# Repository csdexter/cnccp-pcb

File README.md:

#CNC Control Panel: Schematics and Boards#

(C) 2012 Radu - Eosif Mihailescu <radu.mihailescu@linux360.ro>

All files in this repository except `radu-collected.lbr` are licensed under the
**GNU Generic Public License v3**, a copy of whose text can be accessed
 [here](http://www.gnu.org/licenses/gpl.html).

`radu-collected.lbr` alone is hereby licensed under the **Modified BSD (3-clause) License**, a copy of whose text can be found in the `radu-collected.lbr.license` file.

This repository contains [EDA](http://en.wikipedia.org/wiki/Electronic_design_automation) source files for all of the boards in the *CNC Control Panel* project in CadSoft Eagle 6 format. Only the `.SCH` (schematic) and `.BRD` (board) files are provided as all data needed for manufacturing can easily be derived from the former. No guarantee is made as to which minor version of Eagle was used to save the file, but it *may* be the latest at the time of this writing.

The board description files *may* contain routing information or be supplied unrouted. In the former case, the routing artwork *may* have been generated by either Eagle's internal autorouter or [FreeRouting](http://www.freerouting.net/). A 25mil routing grid and 10/10mil trace/space settings will have been used in both cases.

All files included here are compatible with the free version of Eagle (i.e. describe PCBs having no more than 2 layers and measuring no more than 10cm by 8cm each).

Git tags will be used to mark specific revisions that were actually manufactured so that a correspondence between the evolution of the sources and the status of physical by-products can be maintained.

##WARNING##
*Unless and until explictily noted otherwise, the engineering materials here are laboratory quality and neither intended for manufacturing in production quantities nor for distribution (e.g. as kits) to end-users. The design data here does not explicitly follow any widely-accepted safety/security/EMI regulation or standard, therefore any manufacturing and/or usage in connection with live equipment is entirely at your own risk.*

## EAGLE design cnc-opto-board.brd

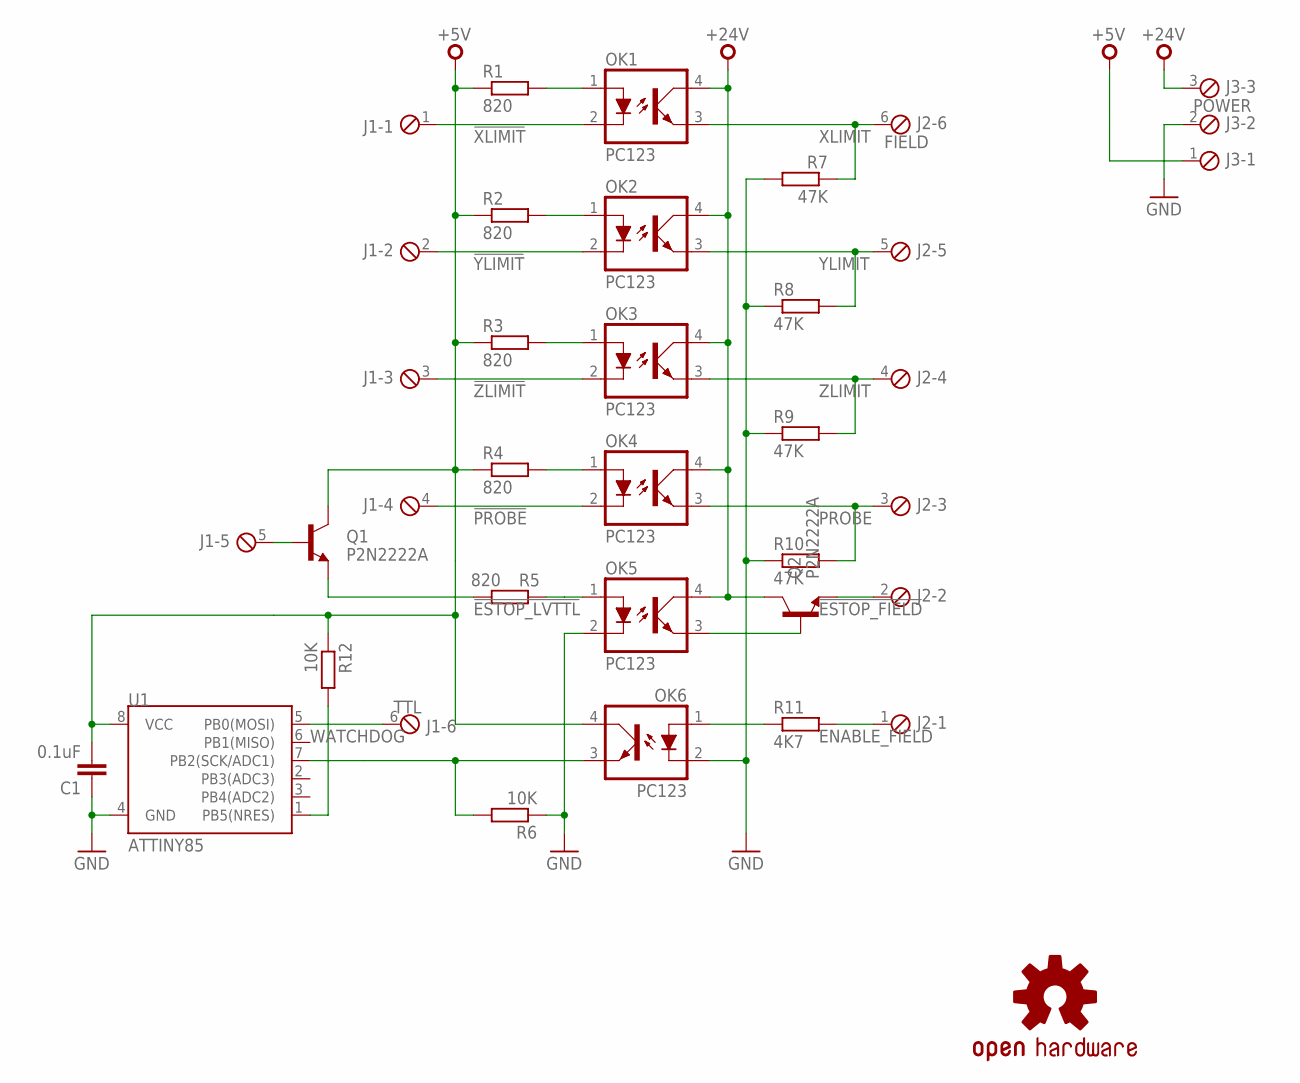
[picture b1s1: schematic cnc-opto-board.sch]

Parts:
C1: 0.1uF; C050-025X075
J1: TTL; MKDS06
J2: FIELD; MKDS06
J3: POWER; MKDS03
LOGO1: OSHW-LOGOL; OSHW-LOGO-L
OK1, OK2, OK3, OK4, OK5, OK6: PC123; DIL04
Q1, Q2: P2N2222A; TO-92
R1, R2, R3, R4, R5: 820; 0207/10
R6, R12: 10K; 0207/10
R7, R8, R9, R10: 47K; 0207/10
R11: 4K7; 0207/10
U1: ATTINY85; DIL08

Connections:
!ESTOP_FIELD: J2.2, Q2.3 (E)
!ESTOP_LVTTL: OK5.1 (A), R5.1
!PROBE: J1.4, OK4.2 (C)
!XLIMIT: J1.1, OK1.2 (C)
!YLIMIT: J1.2, OK2.2 (C)
!ZLIMIT: J1.3, OK3.2 (C)
+5V: C1.2, J3.1, OK6.4 (COL), Q1.1 (C), R1.1, R2.1, R3.1, R4.1, R12.1, U1.8 (VCC)
+24V: J3.3, OK1.4 (COL), OK2.4 (COL), OK3.4 (COL), OK4.4 (COL), OK5.4 (COL), Q2.1 (C)
ENABLE_FIELD: J2.1, R11.2
ENABLE_TTL: OK6.3 (EMIT), R6.2, U1.7 (PB2(SCK/ADC1))
GND: C1.1, J3.2, OK5.2 (C), OK6.2 (C), R6.1, R7.2, R8.1, R9.1, R10.1, U1.4 (GND)
unnamed: OK1.1 (A), R1.2
unnamed: OK2.1 (A), R2.2
unnamed: OK3.1 (A), R3.2
unnamed: OK4.1 (A), R4.2
unnamed: Q1.3 (E), R5.2
unnamed: OK6.1 (A), R11.1
unnamed: J1.5, Q1.2 (B)
unnamed: OK5.3 (EMIT), Q2.2 (B)
unnamed: R12.2, U1.1 (PB5(NRES))
PROBE: J2.3, OK4.3 (EMIT), R10.2
WATCHDOG: J1.6, U1.5 (PB0(MOSI))
XLIMIT: J2.6, OK1.3 (EMIT), R7.1
YLIMIT: J2.5, OK2.3 (EMIT), R8.2
ZLIMIT: J2.4, OK3.3 (EMIT), R9.2

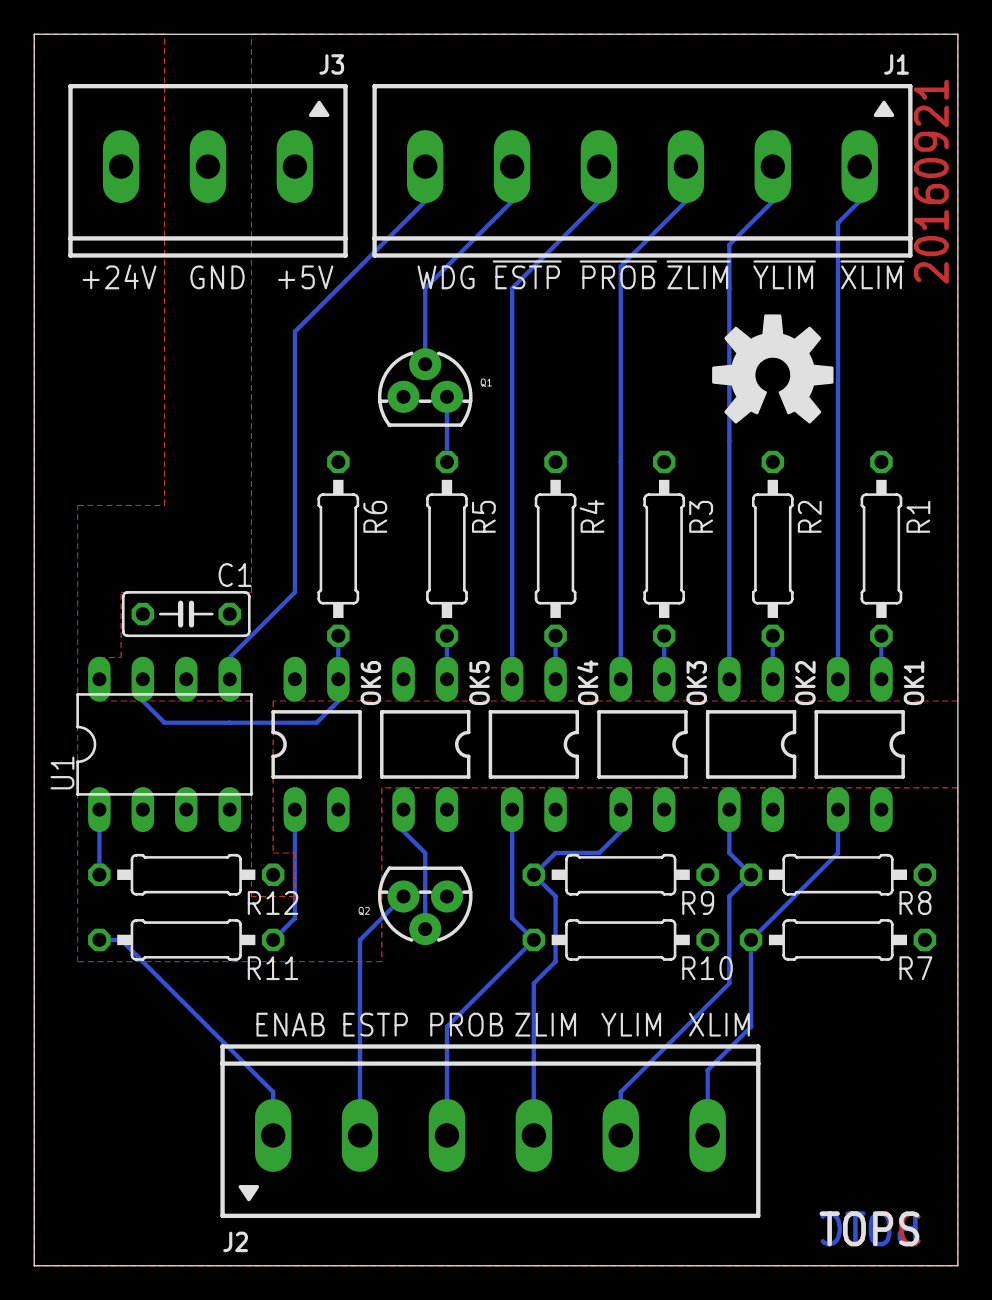
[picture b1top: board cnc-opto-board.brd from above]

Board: 2 copper layers, 54.0 x 72.0 mm, 26 parts (0 on the bottom side), 25 nets.

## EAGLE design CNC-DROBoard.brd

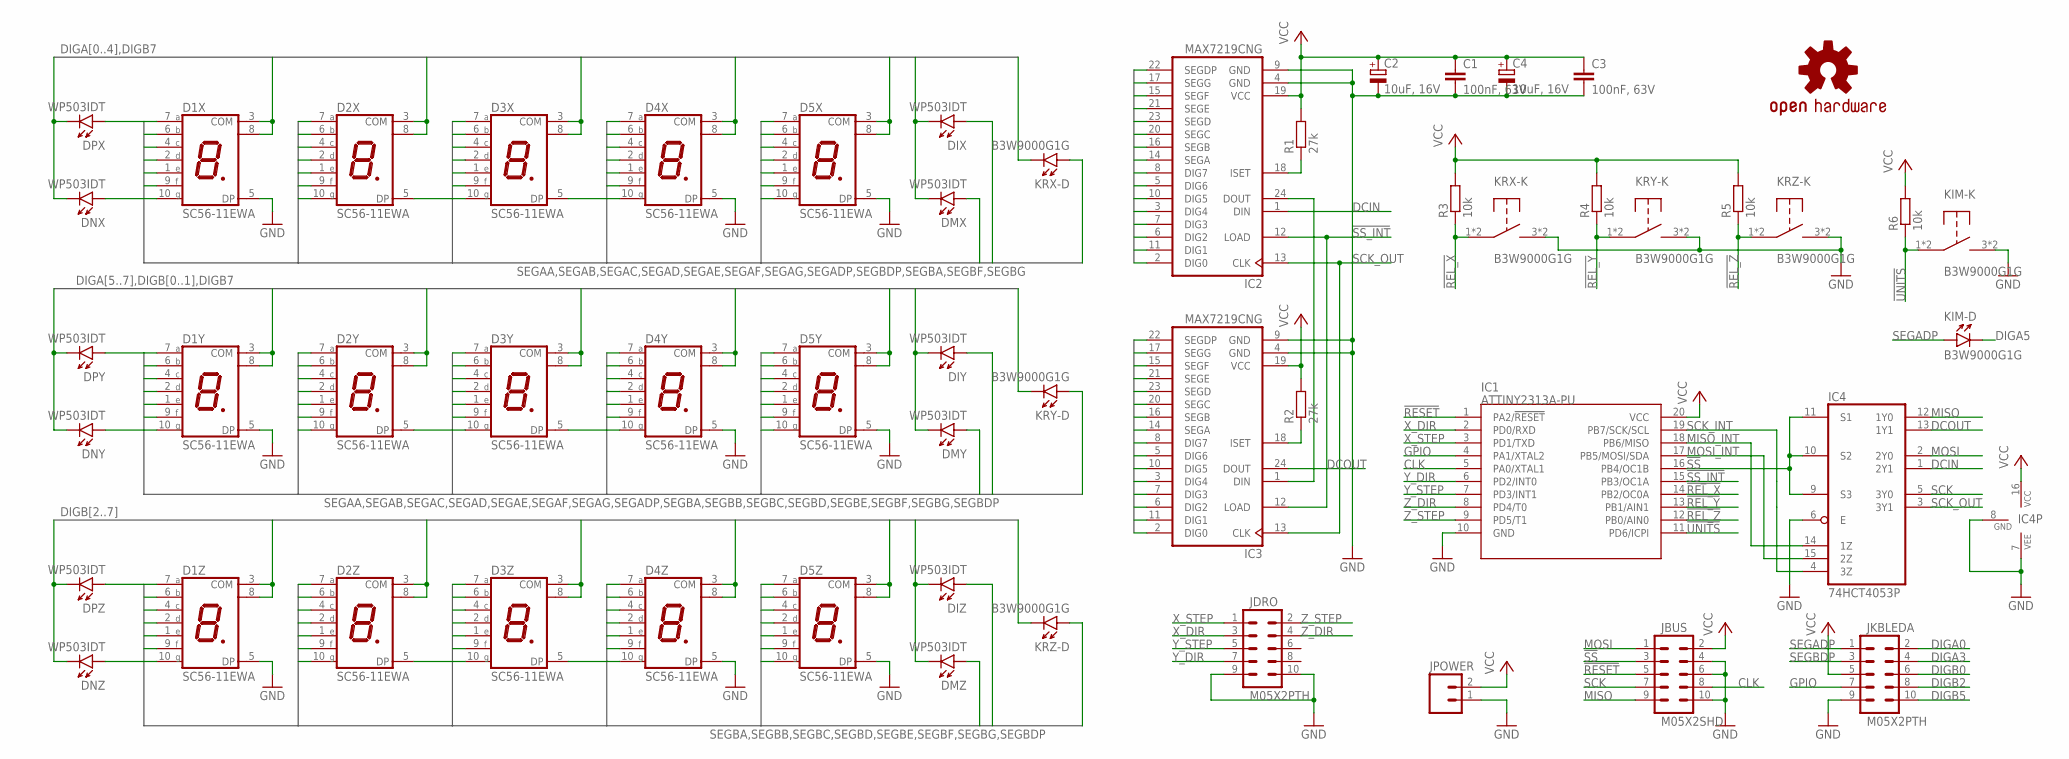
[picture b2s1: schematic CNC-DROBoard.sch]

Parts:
C1, C3: 100nF, 63V; C050-025X075
C2, C4: 10uF, 16V; E2,5-6E
D1X, D1Y, D1Z, D2X, D2Y, D2Z, D3X, D3Y, D3Z, D4X, D4Y, D4Z, D5X, D5Y, D5Z: SC56-11EWA; SA52-11
DIX: WP503IDT; AXIAL__GENERIC_SQ_5X5
DIY: WP503IDT; AXIAL__GENERIC_SQ_5X5
DIZ: WP503IDT; AXIAL__GENERIC_SQ_5X5
DMX: WP503IDT; AXIAL__GENERIC_SQ_5X5
DMY: WP503IDT; AXIAL__GENERIC_SQ_5X5
DMZ: WP503IDT; AXIAL__GENERIC_SQ_5X5
DNX: WP503IDT; AXIAL__GENERIC_SQ_5X5
DNY: WP503IDT; AXIAL__GENERIC_SQ_5X5
DNZ: WP503IDT; AXIAL__GENERIC_SQ_5X5
DPX: WP503IDT; AXIAL__GENERIC_SQ_5X5
DPY: WP503IDT; AXIAL__GENERIC_SQ_5X5
DPZ: WP503IDT; AXIAL__GENERIC_SQ_5X5
IC1: ATTINY2313A-PU; DIL20
IC2, IC3: MAX7219CNG; DIL24-3
IC4: 74HCT4053P; DIL16
JBUS: M05X2SHD; 2X5-SHROUDED
JDRO: M05X2PTH; AVR_ICSP
JKBLEDA: M05X2PTH; AVR_ICSP
JPOWER: M02POLAR; MOLEX-1X2
KIM: B3W9000G1G; OMRON_B3W90
KRX: B3W9000G1G; OMRON_B3W90
KRY: B3W9000G1G; OMRON_B3W90
KRZ: B3W9000G1G; OMRON_B3W90
R1, R2: 27k; 0207/10
R3, R4, R5, R6: 10k; 0207/10
U$1: SPARKFUN_OSHW-LOGOL; SPARKFUN_OSHW-LOGO-L

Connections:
!REL_X: IC1.14 (PB2/OC0A), KRX.1, KRX.2, R3.1
!REL_Y: IC1.13 (PB1/AIN1), KRY.1, KRY.2, R4.1
!REL_Z: IC1.12 (PB0/AIN0), KRZ.1, KRZ.2, R5.1
!RESET: IC1.1 (PA2/!RESET), JBUS.5
!SS: IC1.16 (PB4/OC1B), IC4.9 (S3), IC4.10 (S2), IC4.11 (S1), JBUS.3
!SS_INT: IC1.15 (PB3/OC1A), IC2.12 (LOAD), IC3.12 (LOAD)
!UNITS: IC1.11 (PD6/ICPI), KIM.1, KIM.2, R6.1
CLK: IC1.5 (PA0/XTAL1), JBUS.8
DCIN: IC2.1 (DIN), IC4.1 (2Y1)
DCOUT: IC3.24 (DOUT), IC4.13 (1Y1)
DIGA0: D1X.3 (COM), D1X.8 (COM), IC2.2 (DIG0), JKBLEDA.2
DIGA1: D2X.3 (COM), D2X.8 (COM), IC2.11 (DIG1)
DIGA2: D3X.3 (COM), D3X.8 (COM), IC2.6 (DIG2)
DIGA3: D4X.3 (COM), D4X.8 (COM), IC2.7 (DIG3), JKBLEDA.4
DIGA4: D5X.3 (COM), D5X.8 (COM), IC2.3 (DIG4), KRX.6 (K)
DIGA5: D1Y.3 (COM), D1Y.8 (COM), IC2.10 (DIG5), KIM.6 (K)
DIGA6: D2Y.3 (COM), D2Y.8 (COM), IC2.5 (DIG6)
DIGA7: D3Y.3 (COM), D3Y.8 (COM), IC2.8 (DIG7)
DIGB0: D4Y.3 (COM), D4Y.8 (COM), IC3.2 (DIG0), JKBLEDA.6
DIGB1: D5Y.3 (COM), D5Y.8 (COM), IC3.11 (DIG1), KRY.6 (K)
DIGB2: D1Z.3 (COM), D1Z.8 (COM), IC3.6 (DIG2), JKBLEDA.8
DIGB3: D2Z.3 (COM), D2Z.8 (COM), IC3.7 (DIG3)
DIGB4: D3Z.3 (COM), D3Z.8 (COM), IC3.3 (DIG4)
DIGB5: D4Z.3 (COM), D4Z.8 (COM), IC3.10 (DIG5), JKBLEDA.10
DIGB6: D5Z.3 (COM), D5Z.8 (COM), IC3.5 (DIG6), KRZ.6 (K)
DIGB7: DIX.2 (K), DIY.2 (K), DIZ.2 (K), DMX.2 (K), DMY.2 (K), DMZ.2 (K), DNX.2 (K), DNY.2 (K), DNZ.2 (K), DPX.2 (K), DPY.2 (K), DPZ.2 (K), IC3.8 (DIG7)
GND: C1.2, C2.-, C3.2, C4.-, D1X.5 (DP), D1Y.5 (DP), D1Z.5 (DP), D4X.5 (DP), D4Y.5 (DP), D4Z.5 (DP), D5X.5 (DP), D5Y.5 (DP), D5Z.5 (DP), IC1.10 (GND), IC2.4 (GND), IC2.9 (GND), IC3.4 (GND), IC3.9 (GND), IC4.6 (E), IC4.7 (VEE), IC4.8 (GND), JBUS.4, JBUS.6, JBUS.10, JDRO.9, JDRO.10, JKBLEDA.9, JPOWER.1, KIM.3, KIM.4, KRX.3, KRX.4, KRY.3, KRY.4, KRZ.3, KRZ.4
GPIO: IC1.4 (PA1/XTAL2), JKBLEDA.7
MISO: IC4.12 (1Y0), JBUS.9
MISO_INT: IC1.18 (PB6/MISO), IC4.14 (1Z)
MOSI: IC4.2 (2Y0), JBUS.1
MOSI_INT: IC1.17 (PB5/MOSI/SDA), IC4.15 (2Z)
unnamed: IC2.24 (DOUT), IC3.1 (DIN)
unnamed: IC2.18 (ISET), R1.1
unnamed: IC3.18 (ISET), R2.1
SCK: IC4.5 (3Y0), JBUS.7
SCK_INT: IC1.19 (PB7/SCK/SCL), IC4.4 (3Z)
SCK_OUT: IC2.13 (CLK), IC3.13 (CLK), IC4.3 (3Y1)
SEGAA: D1X.7 (A), D1Y.7 (A), D2X.7 (A), D2Y.7 (A), D3X.7 (A), D3Y.7 (A), D4X.7 (A), D5X.7 (A), IC2.14 (SEGA)
SEGAB: D1X.6 (B), D1Y.6 (B), D2X.6 (B), D2Y.6 (B), D3X.6 (B), D3Y.6 (B), D4X.6 (B), D5X.6 (B), IC2.16 (SEGB)
SEGAC: D1X.4 (C), D1Y.4 (C), D2X.4 (C), D2Y.4 (C), D3X.4 (C), D3Y.4 (C), D4X.4 (C), D5X.4 (C), IC2.20 (SEGC)
SEGAD: D1X.2 (D), D1Y.2 (D), D2X.2 (D), D2Y.2 (D), D3X.2 (D), D3Y.2 (D), D4X.2 (D), D5X.2 (D), IC2.23 (SEGD)
SEGADP: D2X.5 (DP), D2Y.5 (DP), D3X.5 (DP), D3Y.5 (DP), IC2.22 (SEGDP), JKBLEDA.1, KIM.5 (A), KRX.5 (A)
SEGAE: D1X.1 (E), D1Y.1 (E), D2X.1 (E), D2Y.1 (E), D3X.1 (E), D3Y.1 (E), D4X.1 (E), D5X.1 (E), IC2.21 (SEGE)
SEGAF: D1X.9 (F), D1Y.9 (F), D2X.9 (F), D2Y.9 (F), D3X.9 (F), D3Y.9 (F), D4X.9 (F), D5X.9 (F), IC2.15 (SEGF)
SEGAG: D1X.10 (G), D1Y.10 (G), D2X.10 (G), D2Y.10 (G), D3X.10 (G), D3Y.10 (G), D4X.10 (G), D5X.10 (G), IC2.17 (SEGG)
SEGBA: D1Z.7 (A), D2Z.7 (A), D3Z.7 (A), D4Y.7 (A), D4Z.7 (A), D5Y.7 (A), D5Z.7 (A), DNX.1 (A), IC3.14 (SEGA)
SEGBB: D1Z.6 (B), D2Z.6 (B), D3Z.6 (B), D4Y.6 (B), D4Z.6 (B), D5Y.6 (B), D5Z.6 (B), DPY.1 (A), IC3.16 (SEGB)
SEGBC: D1Z.4 (C), D2Z.4 (C), D3Z.4 (C), D4Y.4 (C), D4Z.4 (C), D5Y.4 (C), D5Z.4 (C), DNY.1 (A), IC3.20 (SEGC)
SEGBD: D1Z.2 (D), D2Z.2 (D), D3Z.2 (D), D4Y.2 (D), D4Z.2 (D), D5Y.2 (D), D5Z.2 (D), DPZ.1 (A), IC3.23 (SEGD)
SEGBDP: D2Z.5 (DP), D3Z.5 (DP), DPX.1 (A), IC3.22 (SEGDP), JKBLEDA.3, KRY.5 (A), KRZ.5 (A)
SEGBE: D1Z.1 (E), D2Z.1 (E), D3Z.1 (E), D4Y.1 (E), D4Z.1 (E), D5Y.1 (E), D5Z.1 (E), DNZ.1 (A), IC3.21 (SEGE)
SEGBF: D1Z.9 (F), D2Z.9 (F), D3Z.9 (F), D4Y.9 (F), D4Z.9 (F), D5Y.9 (F), D5Z.9 (F), DIX.1 (A), DIY.1 (A), DIZ.1 (A), IC3.15 (SEGF)
SEGBG: D1Z.10 (G), D2Z.10 (G), D3Z.10 (G), D4Y.10 (G), D4Z.10 (G), D5Y.10 (G), D5Z.10 (G), DMX.1 (A), DMY.1 (A), DMZ.1 (A), IC3.17 (SEGG)
VCC: C1.1, C2.+, C3.1, C4.+, IC1.20 (VCC), IC2.19 (VCC), IC3.19 (VCC), IC4.16 (VCC), JBUS.2, JKBLEDA.5, JPOWER.2, R1.2, R2.2, R3.2, R4.2, R5.2, R6.2
X_DIR: IC1.2 (PD0/RXD), JDRO.3
X_STEP: IC1.3 (PD1/TXD), JDRO.1
Y_DIR: IC1.6 (PD2/INT0), JDRO.7
Y_STEP: IC1.7 (PD3/INT1), JDRO.5
Z_DIR: IC1.8 (PD4/T0), JDRO.4
Z_STEP: IC1.9 (PD5/T1), JDRO.2

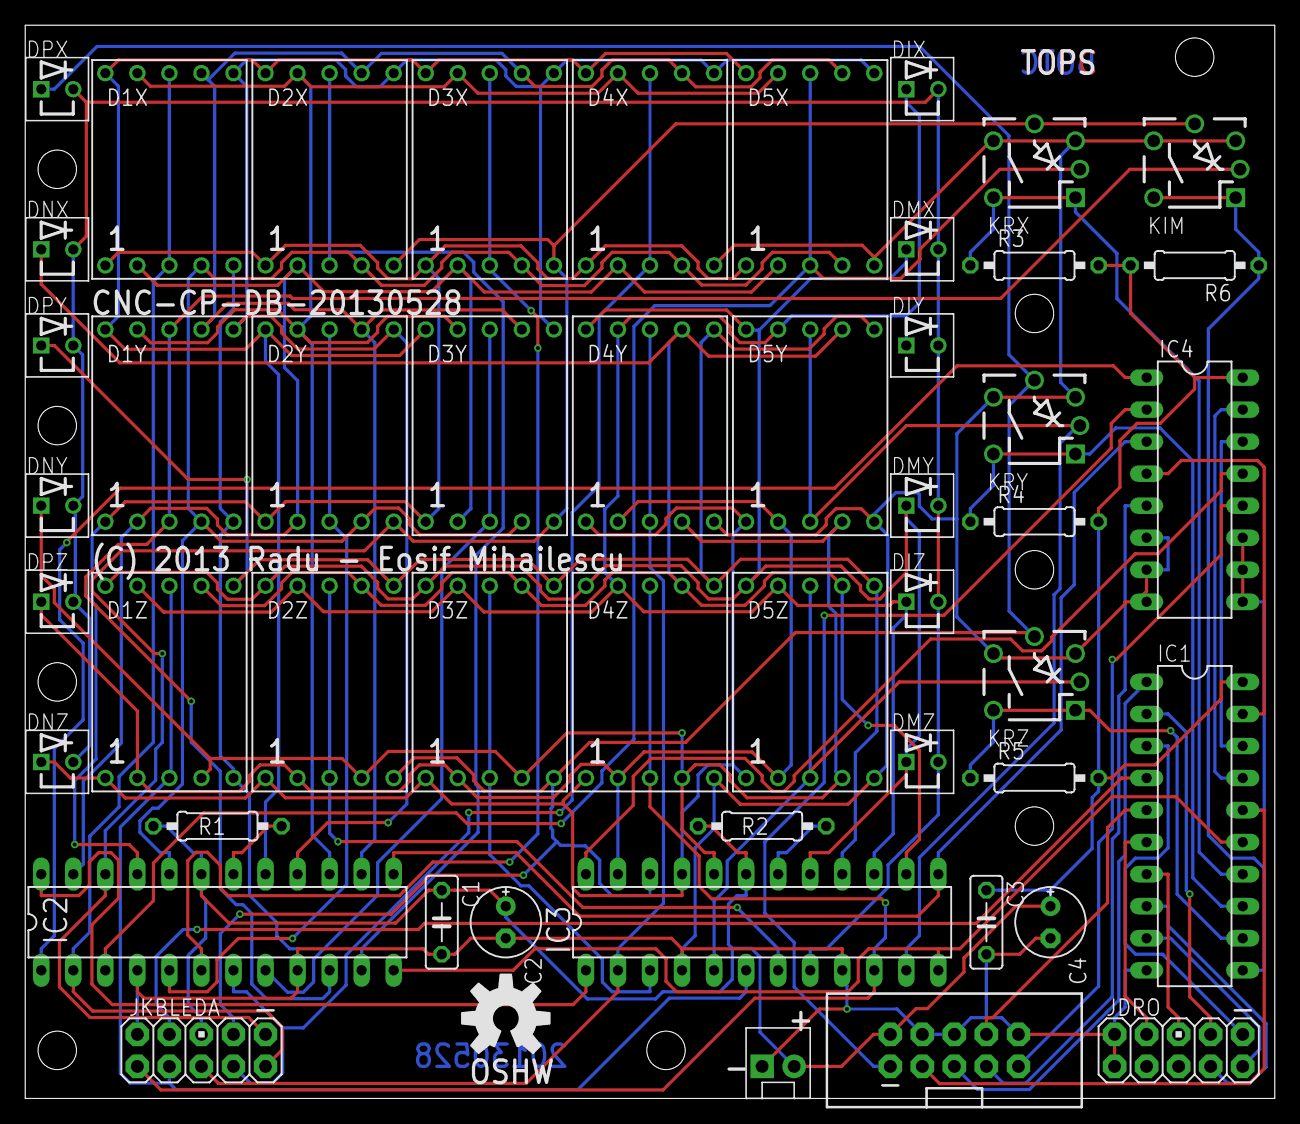
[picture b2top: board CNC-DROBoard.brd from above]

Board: 2 copper layers, 99.1 x 85.1 mm, 50 parts (0 on the bottom side), 61 nets.

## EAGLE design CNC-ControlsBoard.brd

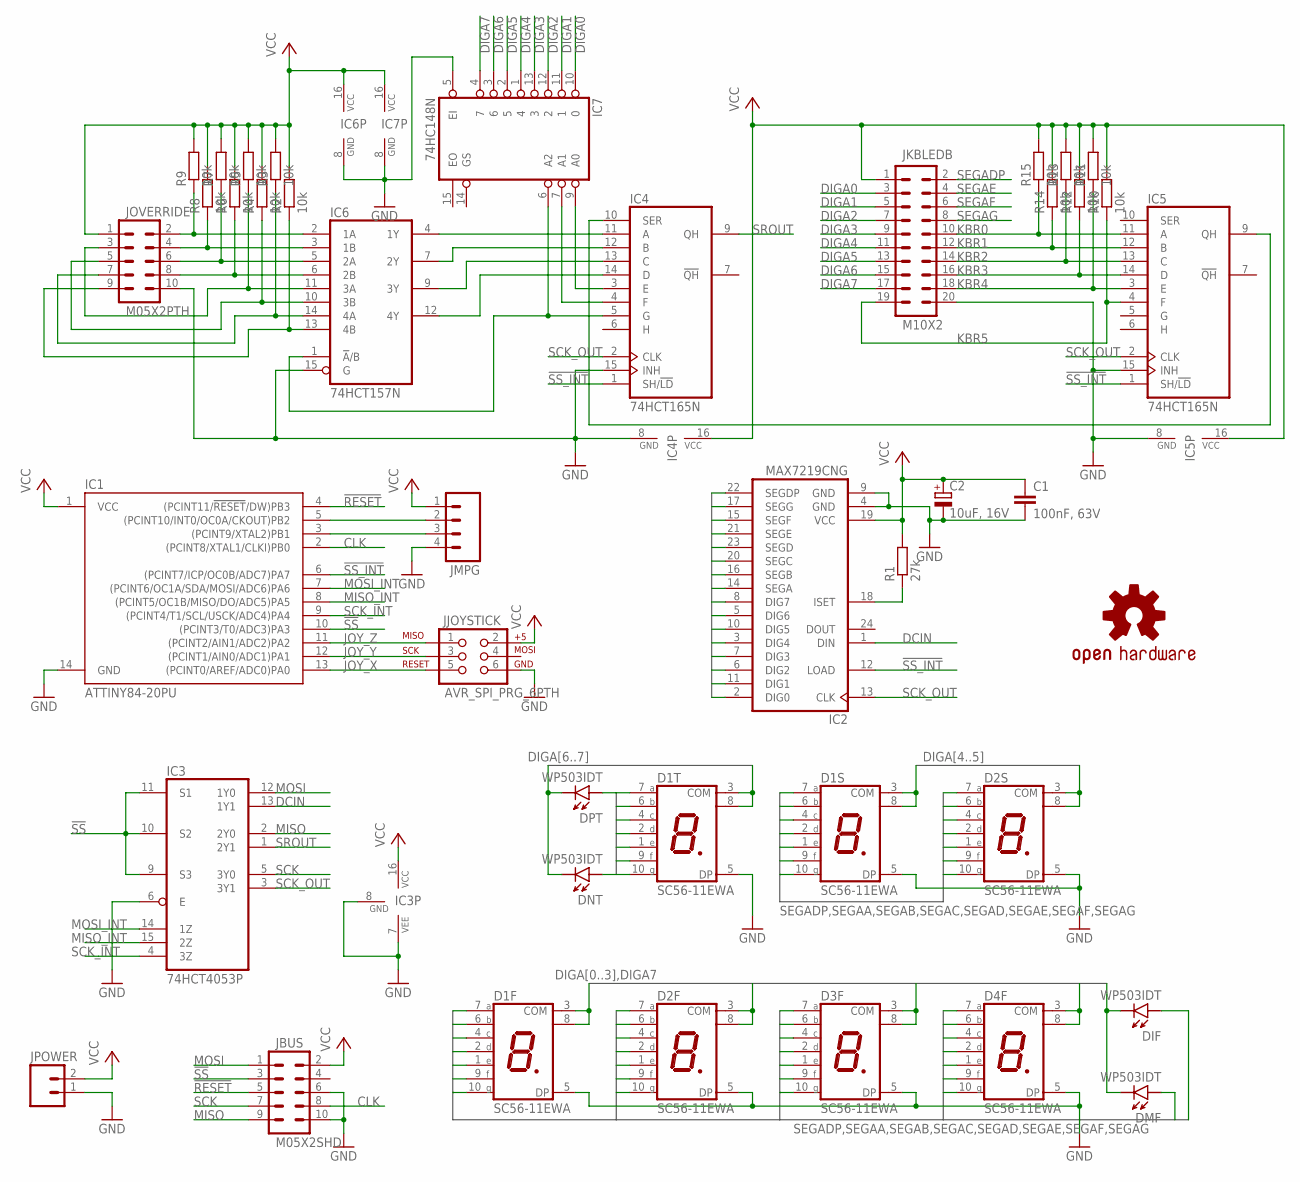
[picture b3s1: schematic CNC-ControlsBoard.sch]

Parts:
C1: 100nF, 63V; C050-025X075
C2: 10uF, 16V; E2,5-6E
D1F, D1S, D1T, D2F, D2S, D3F, D4F: SC56-11EWA; SA52-11
DIF: WP503IDT; AXIAL__GENERIC_SQ_5X5
DMF: WP503IDT; AXIAL__GENERIC_SQ_5X5
DNT: WP503IDT; AXIAL__GENERIC_SQ_5X5
DPT: WP503IDT; AXIAL__GENERIC_SQ_5X5
IC1: ATTINY84-20PU; DIL14
IC2: MAX7219CNG; DIL24-3
IC3: 74HCT4053P; DIL16
IC4, IC5: 74HCT165N; DIL16
IC6: 74HCT157N; DIL16
IC7: 74HC148N; DIL16
JBUS: M05X2SHD; 2X5-SHROUDED
JJOYSTICK: AVR_SPI_PRG_6PTH; 2X3
JKBLEDB: M10X2; 2X10
JMPG: M04PTH; 1X04
JOVERRIDE: M05X2PTH; AVR_ICSP
JPOWER: M02POLAR; MOLEX-1X2
R1: 27k; 0207/10
R2, R3, R4, R5, R6, R7, R8, R9, R10, R11, R12, R13, R14, R15: 10k; 0207/10
U$1: SPARKFUN_OSHW-LOGOL; SPARKFUN_OSHW-LOGO-L

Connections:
!RESET: IC1.4 ((PCINT11/!RESET!/DW)PB3), JBUS.5
!SS: IC1.10 ((PCINT3/T0/ADC3)PA3), IC3.9 (S3), IC3.10 (S2), IC3.11 (S1), JBUS.3
!SS_INT: IC1.6 ((PCINT7/ICP/OC0B/ADC7)PA7), IC2.12 (LOAD), IC4.1 (SH/!LD), IC5.1 (SH/!LD)
CLK: IC1.2 ((PCINT8/XTAL1/CLKI)PB0), JBUS.8
DCIN: IC2.1 (DIN), IC3.13 (1Y1)
DIGA0: D1F.3 (COM), D1F.8 (COM), IC2.2 (DIG0), IC7.10 (0), JKBLEDB.3
DIGA1: D2F.3 (COM), D2F.8 (COM), IC2.11 (DIG1), IC7.11 (1), JKBLEDB.5
DIGA2: D3F.3 (COM), D3F.8 (COM), IC2.6 (DIG2), IC7.12 (2), JKBLEDB.7
DIGA3: D4F.3 (COM), D4F.8 (COM), IC2.7 (DIG3), IC7.13 (3), JKBLEDB.9
DIGA4: D1S.3 (COM), D1S.8 (COM), IC2.3 (DIG4), IC7.1 (4), JKBLEDB.11
DIGA5: D2S.3 (COM), D2S.8 (COM), IC2.10 (DIG5), IC7.2 (5), JKBLEDB.13
DIGA6: D1T.3 (COM), D1T.8 (COM), IC2.5 (DIG6), IC7.3 (6), JKBLEDB.15
DIGA7: DIF.2 (K), DMF.2 (K), DNT.2 (K), DPT.2 (K), IC2.8 (DIG7), IC7.4 (7), JKBLEDB.17
FOA1: IC6.13 (4B), JOVERRIDE.9, R2.1
FOB1: IC6.14 (4A), JOVERRIDE.7, R3.1
FOC1: IC6.10 (3B), JOVERRIDE.5, R4.1
FOD1: IC6.11 (3A), JOVERRIDE.3, R5.1
GND: C1.2, C2.-, D1F.5 (DP), D1S.5 (DP), D1T.5 (DP), D2F.5 (DP), D2S.5 (DP), D3F.5 (DP), D4F.5 (DP), IC1.14 (GND), IC2.4 (GND), IC2.9 (GND), IC3.6 (E), IC3.7 (VEE), IC3.8 (GND), IC4.8 (GND), IC4.15 (INH), IC5.8 (GND), IC5.15 (INH), IC6.8 (GND), IC6.15 (G), IC7.5 (EI), IC7.8 (GND), JBUS.6, JBUS.10, JJOYSTICK.6, JKBLEDB.20, JMPG.4, JOVERRIDE.10, JPOWER.1
JOY_X: IC1.13 ((PCINT0/AREF/ADC0)PA0), JJOYSTICK.5
JOY_Y: IC1.12 ((PCINT1/AIN0/ADC1)PA1), JJOYSTICK.3
JOY_Z: IC1.11 ((PCINT2/AIN1/ADC2)PA2), JJOYSTICK.1
KBR0: IC5.11 (A), JKBLEDB.10, R15.1
KBR1: IC5.12 (B), JKBLEDB.12, R14.1
KBR2: IC5.13 (C), JKBLEDB.14, R13.1
KBR3: IC5.14 (D), JKBLEDB.16, R12.1
KBR4: IC5.3 (E), JKBLEDB.18, R11.1
KBR5: IC5.4 (F), JKBLEDB.19, R10.1
MISO: IC3.2 (2Y0), JBUS.9
MISO_INT: IC1.8 ((PCINT5/OC1B/MISO/DO/ADC5)PA5), IC3.15 (2Z)
MOSI: IC3.12 (1Y0), JBUS.1
MOSI_INT: IC1.7 ((PCINT6/OC1A/SDA/MOSI/ADC6)PA6), IC3.14 (1Z)
unnamed: IC4.10 (SER), IC5.9 (QH)
unnamed: IC4.11 (A), IC6.4 (1Y)
unnamed: IC4.12 (B), IC6.7 (2Y)
unnamed: IC1.5 ((PCINT10/INT0/OC0A/CKOUT)PB2), JMPG.2
unnamed: IC1.3 ((PCINT9/XTAL2)PB1), JMPG.3
unnamed: IC4.13 (C), IC6.9 (3Y)
unnamed: IC4.14 (D), IC6.12 (4Y)
unnamed: IC4.3 (E), IC7.9 (A0)
unnamed: IC4.4 (F), IC7.7 (A1)
unnamed: IC4.5 (G), IC6.1 (!A!/B), IC7.6 (A2)
unnamed: IC2.18 (ISET), R1.1
SCK: IC3.5 (3Y0), JBUS.7
SCK_INT: IC1.9 ((PCINT4/T1/SCL/USCK/ADC4)PA4), IC3.4 (3Z)
SCK_OUT: IC2.13 (CLK), IC3.3 (3Y1), IC4.2 (CLK), IC5.2 (CLK)
SEGAA: D1F.7 (A), D1S.7 (A), D1T.7 (A), D2F.7 (A), D2S.7 (A), D3F.7 (A), D4F.7 (A), DPT.1 (A), IC2.14 (SEGA)
SEGAB: D1F.6 (B), D1S.6 (B), D1T.6 (B), D2F.6 (B), D2S.6 (B), D3F.6 (B), D4F.6 (B), DNT.1 (A), IC2.16 (SEGB)
SEGAC: D1F.4 (C), D1S.4 (C), D1T.4 (C), D2F.4 (C), D2S.4 (C), D3F.4 (C), D4F.4 (C), DIF.1 (A), IC2.20 (SEGC)
SEGAD: D1F.2 (D), D1S.2 (D), D1T.2 (D), D2F.2 (D), D2S.2 (D), D3F.2 (D), D4F.2 (D), DMF.1 (A), IC2.23 (SEGD)
SEGADP: IC2.22 (SEGDP), JKBLEDB.2
SEGAE: D1F.1 (E), D1S.1 (E), D1T.1 (E), D2F.1 (E), D2S.1 (E), D3F.1 (E), D4F.1 (E), IC2.21 (SEGE), JKBLEDB.4
SEGAF: D1F.9 (F), D1S.9 (F), D1T.9 (F), D2F.9 (F), D2S.9 (F), D3F.9 (F), D4F.9 (F), IC2.15 (SEGF), JKBLEDB.6
SEGAG: D1F.10 (G), D1S.10 (G), D1T.10 (G), D2F.10 (G), D2S.10 (G), D3F.10 (G), D4F.10 (G), IC2.17 (SEGG), JKBLEDB.8
SOA1: IC6.6 (2B), JOVERRIDE.8, R6.1
SOB1: IC6.5 (2A), JOVERRIDE.6, R7.1
SOC1: IC6.3 (1B), JOVERRIDE.4, R8.1
SOD1: IC6.2 (1A), JOVERRIDE.2, R9.1
SROUT: IC3.1 (2Y1), IC4.9 (QH)
VCC: C1.1, C2.+, IC1.1 (VCC), IC2.19 (VCC), IC3.16 (VCC), IC4.16 (VCC), IC5.16 (VCC), IC6.16 (VCC), IC7.16 (VCC), JBUS.2, JJOYSTICK.2, JKBLEDB.1, JMPG.1, JOVERRIDE.1, JPOWER.2, R1.2, R2.2, R3.2, R4.2, R5.2, R6.2, R7.2, R8.2, R9.2, R10.2, R11.2, R12.2, R13.2, R14.2, R15.2

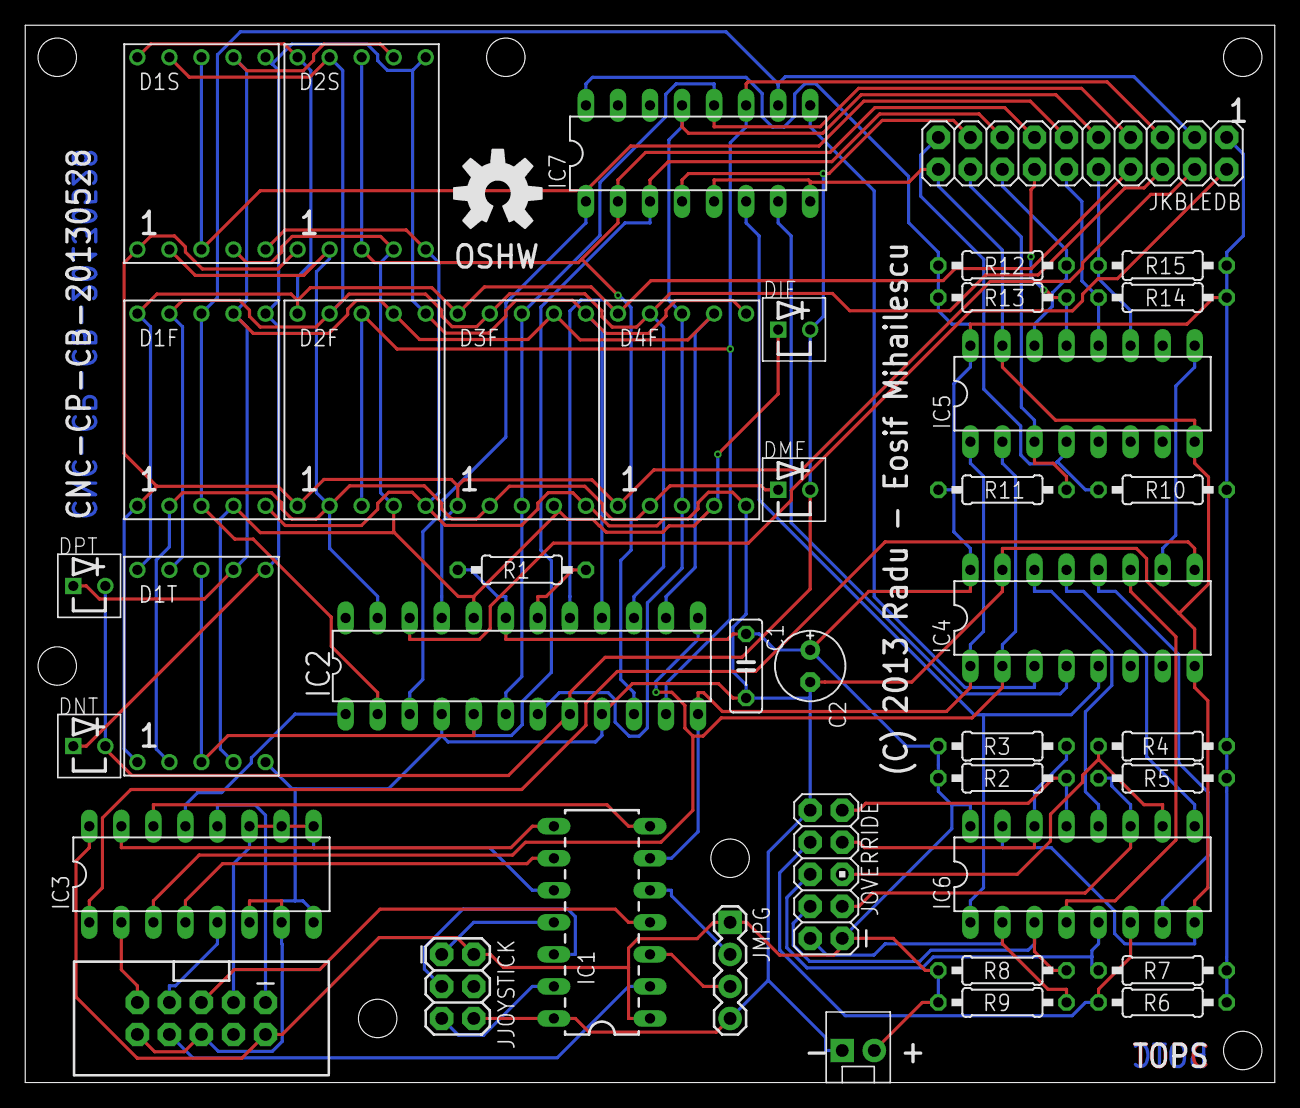
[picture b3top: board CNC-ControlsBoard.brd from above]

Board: 2 copper layers, 99.1 x 83.8 mm, 42 parts (0 on the bottom side), 59 nets.

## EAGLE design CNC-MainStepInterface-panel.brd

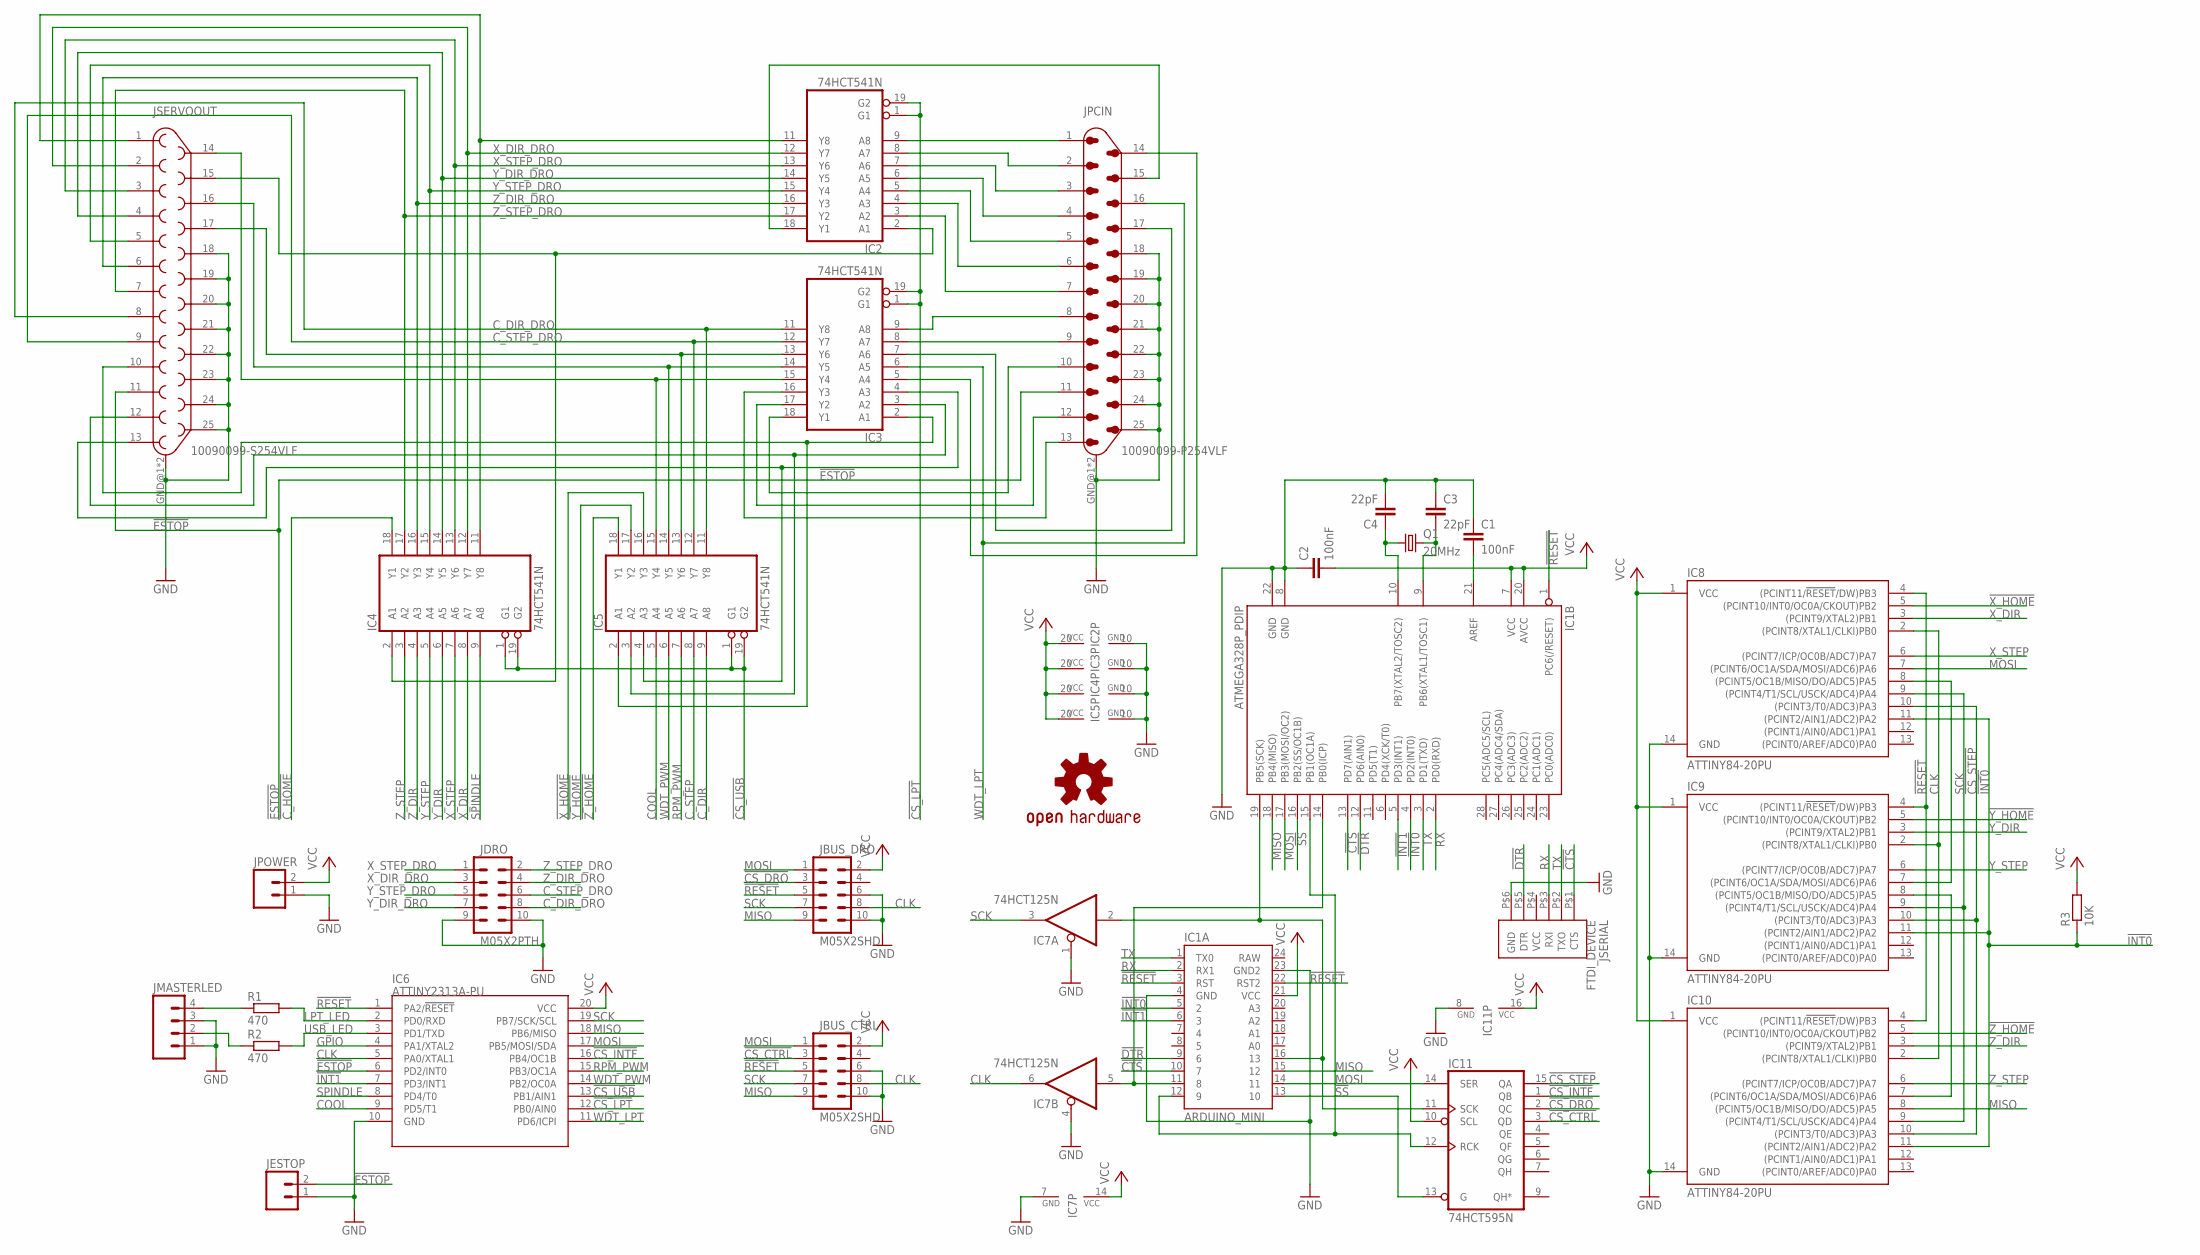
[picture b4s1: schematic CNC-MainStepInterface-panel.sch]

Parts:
C1, C2: 100nF; C050-025X075
C3, C4: 22pF; C050-025X075
IC1A: ARDUINO_MINI
IC1B: ATMEGA328P_PDIP; DIL28-3
IC2, IC3, IC4, IC5: 74HCT541N; DIL20
IC6: ATTINY2313A-PU; DIL20
IC7: 74HCT125N; DIL14
IC8, IC9, IC10: ATTINY84-20PU; DIL14
IC11: 74HCT595N; DIL16
JBUS_CTRL: M05X2SHD; 2X5-SHROUDED
JBUS_DRO: M05X2SHD; 2X5-SHROUDED
JDRO: M05X2PTH; AVR_ICSP
JESTOP: M02PTH; 1X02
JMASTERLED: M04PTH; 1X04
JPCIN: 10090099-P254VLF
JPOWER: M02POLAR; MOLEX-1X2
JSERIAL: FTDI_DEVICE; FTDI_DEVICE_SIDE
JSERVOOUT: 10090099-S254VLF
Q1: 20MHz; HC49U-V
R1, R2: 470; 0207/10
R3: 10K; 0207/10
U$1: SPARKFUN_OSHW-LOGOL; SPARKFUN_OSHW-LOGO-L

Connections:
!CS_CTRL: IC11.3 (QD), JBUS_CTRL.3
!CS_DRO: IC11.2 (QC), JBUS_DRO.3
!CS_INTF: IC6.16 (PB4/OC1B), IC11.1 (QB)
!CS_LPT: IC2.1 (G1), IC2.19 (G2), IC3.1 (G1), IC3.19 (G2), IC6.12 (PB0/AIN0)
!CS_STEP: IC8.10 ((PCINT3/T0/ADC3)PA3), IC9.10 ((PCINT3/T0/ADC3)PA3), IC10.10 ((PCINT3/T0/ADC3)PA3), IC11.15 (QA)
!CS_USB: IC4.1 (G1), IC4.19 (G2), IC5.1 (G1), IC5.19 (G2), IC6.13 (PB1/AIN1)
!CTS: IC1A.10 (7), IC1B.13 (PD7(AIN1)), JSERIAL.P$1 (CTS)
!C_HOME: IC4.18 (Y1)
!DTR: IC1A.9 (6), IC1B.12 (PD6(AIN0)), JSERIAL.P$5 (DTR)
!ESTOP: IC6.6 (PD2/INT0), JESTOP.2, JPCIN.11, JSERVOOUT.11
!INT0: IC1A.5 (2), IC1B.4 (PD2(INT0)), IC8.11 ((PCINT2/AIN1/ADC2)PA2), IC9.11 ((PCINT2/AIN1/ADC2)PA2), IC10.11 ((PCINT2/AIN1/ADC2)PA2), R3.1
!INT1: IC1A.6 (3), IC1B.5 (PD3(INT1)), IC6.7 (PD3/INT1)
!RESET: IC1A.3 (RST), IC1A.22 (RST2), IC1B.1 (PC6(/RESET)), IC6.1 (PA2/!RESET), IC8.4 ((PCINT11/!RESET!/DW)PB3), IC9.4 ((PCINT11/!RESET!/DW)PB3), IC10.4 ((PCINT11/!RESET!/DW)PB3), JBUS_CTRL.5, JBUS_DRO.5
!SS: IC1A.13 (10), IC1B.16 (PB2(SS/OC1B)), IC11.13 (G)
!X_HOME: IC5.16 (Y3), IC8.5 ((PCINT10/INT0/OC0A/CKOUT)PB2)
!Y_HOME: IC5.17 (Y2), IC9.5 ((PCINT10/INT0/OC0A/CKOUT)PB2)
!Z_HOME: IC5.18 (Y1), IC10.5 ((PCINT10/INT0/OC0A/CKOUT)PB2)
CLK: IC6.5 (PA0/XTAL1), IC7.6 (O), IC8.2 ((PCINT8/XTAL1/CLKI)PB0), IC9.2 ((PCINT8/XTAL1/CLKI)PB0), IC10.2 ((PCINT8/XTAL1/CLKI)PB0), JBUS_CTRL.8, JBUS_DRO.8
CLK_INT: IC1A.11 (8), IC1B.14 (PB0(ICP)), IC7.5 (I)
COOL: IC5.5 (A4), IC6.9 (PD5/T1)
C_DIR: IC5.9 (A8)
C_DIR_DRO: IC3.11 (Y8), IC5.11 (Y8), JDRO.8, JSERVOOUT.8
C_STEP: IC5.8 (A7)
C_STEP_DRO: IC3.12 (Y7), IC5.12 (Y7), JDRO.6, JSERVOOUT.9
GND: C1.1, C2.1, C3.1, C4.2, IC1A.4 (GND), IC1A.23 (GND2), IC1B.8 (GND), IC1B.22 (GND), IC2.10 (GND), IC3.10 (GND), IC4.10 (GND), IC5.10 (GND), IC6.10 (GND), IC7.1 (OE), IC7.4 (OE), IC7.7 (GND), IC8.14 (GND), IC9.14 (GND), IC10.14 (GND), IC11.8 (GND), JBUS_CTRL.6, JBUS_CTRL.10, JBUS_DRO.6, JBUS_DRO.10, JDRO.9, JDRO.10, JESTOP.1, JMASTERLED.1, JMASTERLED.3, JPCIN.18, JPCIN.19, JPCIN.20, JPCIN.21, JPCIN.22, JPCIN.23, JPCIN.24, JPCIN.25, JPCIN.GND@1 (GND), JPCIN.GND@2 (GND), JPOWER.1, JSERIAL.P$6 (GND), JSERVOOUT.18, JSERVOOUT.19, JSERVOOUT.20, JSERVOOUT.21, JSERVOOUT.22, JSERVOOUT.23, JSERVOOUT.24, JSERVOOUT.25, JSERVOOUT.GND@1 (GND), JSERVOOUT.GND@2 (GND)
GPIO: IC6.4 (PA1/XTAL2)
LPT_LED: IC6.2 (PD0/RXD), R1.2
MISO: IC1A.15 (12), IC1B.18 (PB4(MISO)), IC6.18 (PB6/MISO), IC10.8 ((PCINT5/OC1B/MISO/DO/ADC5)PA5), JBUS_CTRL.9, JBUS_DRO.9
MISO_1: IC8.8 ((PCINT5/OC1B/MISO/DO/ADC5)PA5), IC9.7 ((PCINT6/OC1A/SDA/MOSI/ADC6)PA6)
MISO_2: IC9.8 ((PCINT5/OC1B/MISO/DO/ADC5)PA5), IC10.7 ((PCINT6/OC1A/SDA/MOSI/ADC6)PA6)
MOSI: IC1A.14 (11), IC1B.17 (PB3(MOSI/OC2)), IC6.17 (PB5/MOSI/SDA), IC8.7 ((PCINT6/OC1A/SDA/MOSI/ADC6)PA6), IC11.14 (SER), JBUS_CTRL.1, JBUS_DRO.1
unnamed: IC2.9 (A8), JPCIN.1
unnamed: IC2.8 (A7), JPCIN.2
unnamed: IC2.7 (A6), JPCIN.3
unnamed: IC2.6 (A5), JPCIN.4
unnamed: IC2.5 (A4), JPCIN.5
unnamed: IC2.4 (A3), JPCIN.6
unnamed: IC2.3 (A2), JPCIN.7
unnamed: IC3.9 (A8), JPCIN.8
unnamed: IC3.8 (A7), JPCIN.9
unnamed: IC3.5 (A4), JPCIN.14
unnamed: JMASTERLED.2, R2.1
unnamed: IC3.2 (A1), IC5.2 (A1), JSERVOOUT.10
unnamed: IC3.3 (A2), IC5.3 (A2), JSERVOOUT.12
unnamed: IC3.7 (A6), JPCIN.17
unnamed: IC3.4 (A3), IC5.4 (A3), JSERVOOUT.13
unnamed: JMASTERLED.4, R1.1
unnamed: IC3.16 (Y3), JPCIN.13
unnamed: IC3.17 (Y2), JPCIN.12
unnamed: IC2.18 (Y1), JPCIN.15
unnamed: C1.2, IC1B.21 (AREF)
unnamed: IC3.18 (Y1), JPCIN.10
unnamed: IC3.15 (Y4), IC5.15 (Y4), JSERVOOUT.14
unnamed: IC3.14 (Y5), IC5.14 (Y5), JSERVOOUT.16
unnamed: IC3.13 (Y6), IC5.13 (Y6), JSERVOOUT.17
unnamed: IC2.2 (A1), IC4.2 (A1), JSERVOOUT.15
unnamed: IC2.11 (Y8), IC4.11 (Y8), JSERVOOUT.1
RPM_PWM: IC5.7 (A6), IC6.15 (PB3/OC1A)
RX: IC1A.2 (RX1), IC1B.2 (PD0(RXD)), JSERIAL.P$3 (RXI)
SADDR: IC1A.12 (9), IC1B.15 (PB1(OC1A)), IC11.12 (RCK)
SCK: IC6.19 (PB7/SCK/SCL), IC7.3 (O), IC8.9 ((PCINT4/T1/SCL/USCK/ADC4)PA4), IC9.9 ((PCINT4/T1/SCL/USCK/ADC4)PA4), IC10.9 ((PCINT4/T1/SCL/USCK/ADC4)PA4), JBUS_CTRL.7, JBUS_DRO.7
SCK_INT: IC1A.16 (13), IC1B.19 (PB5(SCK)), IC7.2 (I), IC11.11 (SCK)
SPINDLE: IC4.9 (A8), IC6.8 (PD4/T0)
TX: IC1A.1 (TX0), IC1B.3 (PD1(TXD)), JSERIAL.P$2 (TXO)
USB_LED: IC6.3 (PD1/TXD), R2.2
VCC: C2.2, IC1A.21 (VCC), IC1B.7 (VCC), IC1B.20 (AVCC), IC2.20 (VCC), IC3.20 (VCC), IC4.20 (VCC), IC5.20 (VCC), IC6.20 (VCC), IC7.14 (VCC), IC8.1 (VCC), IC9.1 (VCC), IC10.1 (VCC), IC11.10 (SCL), IC11.16 (VCC), JBUS_CTRL.2, JBUS_DRO.2, JPOWER.2, R3.2
WDT_LPT: IC3.6 (A5), IC6.11 (PD6/ICPI), JPCIN.16
WDT_PWM: IC5.6 (A5), IC6.14 (PB2/OC0A)
XTAL1: C4.1, IC1B.10 (PB7(XTAL2/TOSC2)), Q1.1
XTAL2: C3.2, IC1B.9 (PB6(XTAL1/TOSC1)), Q1.2
X_DIR: IC4.8 (A7), IC8.3 ((PCINT9/XTAL2)PB1)
X_DIR_DRO: IC2.12 (Y7), IC4.12 (Y7), JDRO.3, JSERVOOUT.2
X_STEP: IC4.7 (A6), IC8.6 ((PCINT7/ICP/OC0B/ADC7)PA7)
X_STEP_DRO: IC2.13 (Y6), IC4.13 (Y6), JDRO.1, JSERVOOUT.3
Y_DIR: IC4.6 (A5), IC9.3 ((PCINT9/XTAL2)PB1)
Y_DIR_DRO: IC2.14 (Y5), IC4.14 (Y5), JDRO.7, JSERVOOUT.4
Y_STEP: IC4.5 (A4), IC9.6 ((PCINT7/ICP/OC0B/ADC7)PA7)
Y_STEP_DRO: IC2.15 (Y4), IC4.15 (Y4), JDRO.5, JSERVOOUT.5
Z_DIR: IC4.4 (A3), IC10.3 ((PCINT9/XTAL2)PB1)
Z_DIR_DRO: IC2.16 (Y3), IC4.16 (Y3), JDRO.4, JSERVOOUT.6
Z_STEP: IC4.3 (A2), IC10.6 ((PCINT7/ICP/OC0B/ADC7)PA7)
Z_STEP_DRO: IC2.17 (Y2), IC4.17 (Y2), JDRO.2, JSERVOOUT.7

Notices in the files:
CNC-ControlsBoard.brd:
(C) 2013 Radu - Eosif Mihailescu
cnc-opto-board.brd:
(C) 2016 Radu - Eosif Mihailescu
parts and their libraries:
SparkFun-DigitalIC-mine: Licensing: CC v3.0 Share-Alike You are welcome to use this library for commercial purposes.
SparkFun-DiscreteSemi: Licensing: Creative Commons ShareAlike 4.0 International - https://creativecommons.org/licenses/by-sa/4.0
